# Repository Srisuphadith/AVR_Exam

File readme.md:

# Oscilloscope and Component tester
### CPE324 Embedded System
### Member
- 66070501027 NOPPANUT PRASERTWONGSA
- 66070501052 SRISUPHADITH RATTANAPRASERT
- 66070501053 SAKCHAT HENSOOK
- 66070501060 ADISORN PARAMA

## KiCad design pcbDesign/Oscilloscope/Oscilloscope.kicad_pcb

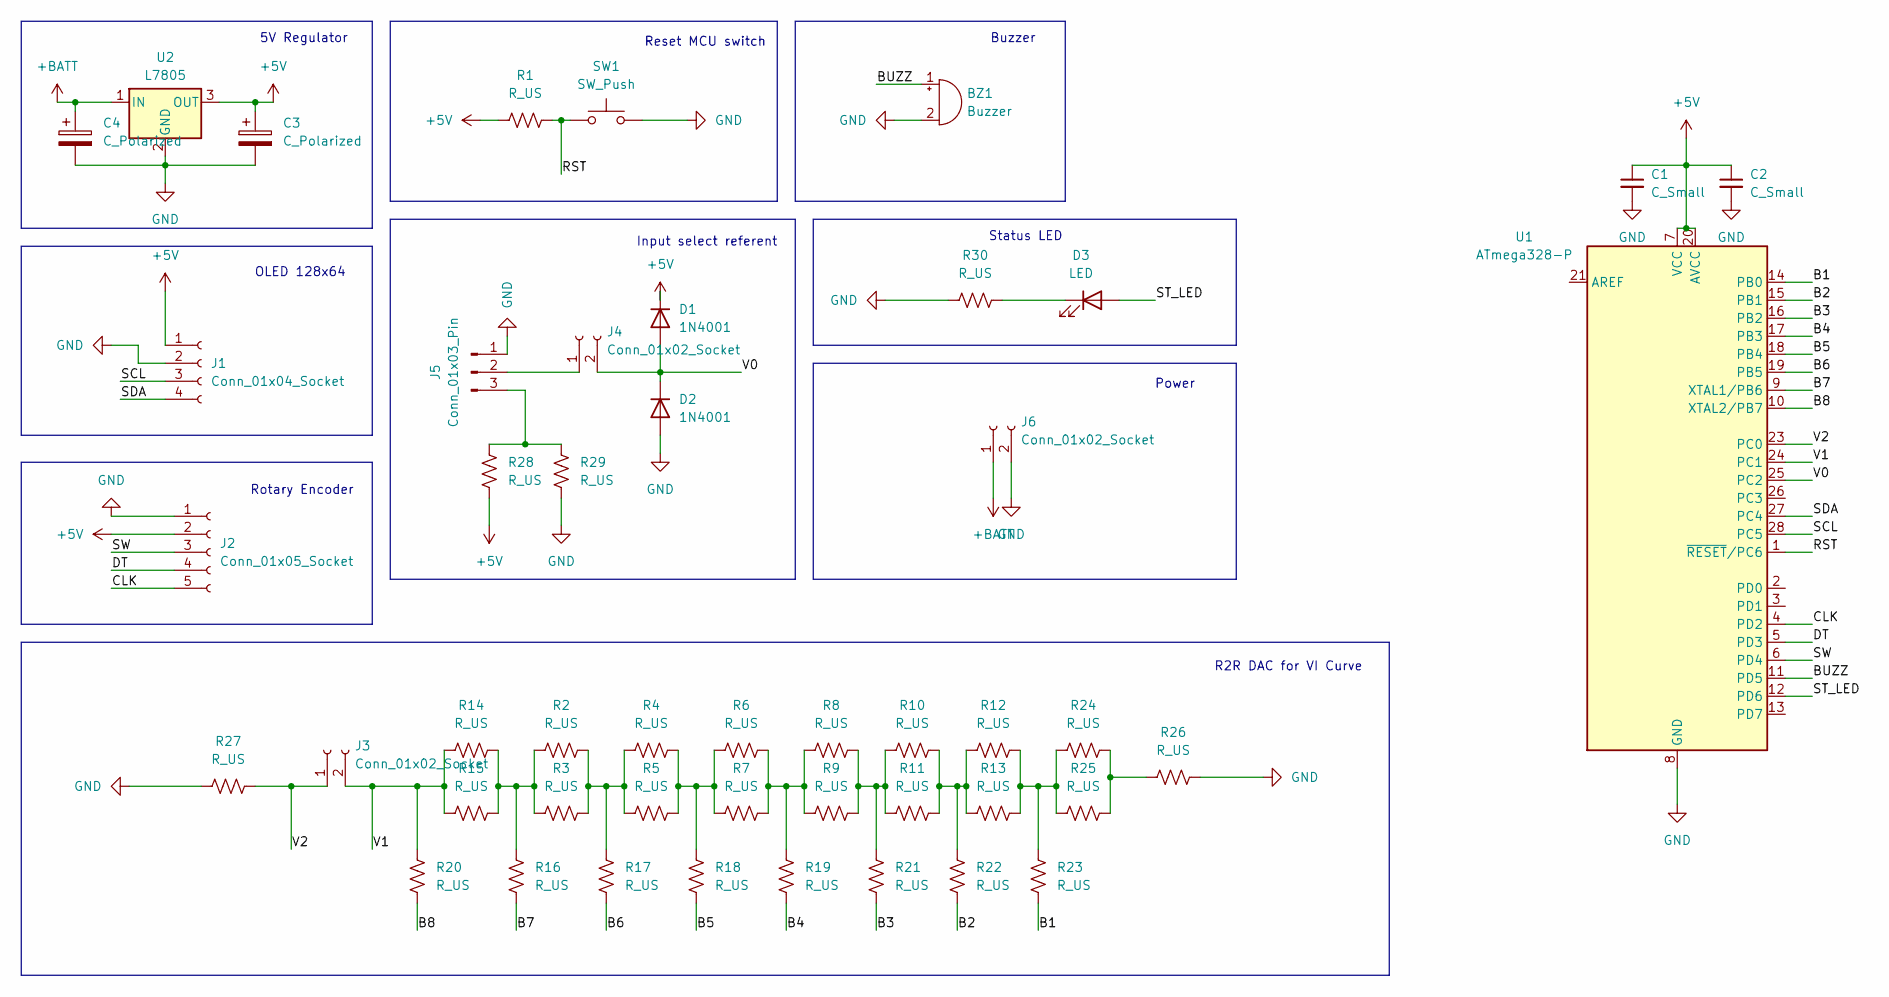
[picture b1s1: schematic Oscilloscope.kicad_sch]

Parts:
BZ1: Buzzer; Buzzer_12x9.5RM7.6
C1, C2: C_Small; C_Disc_D6.0mm_W2.5mm_P5.00mm
C3, C4: C_Polarized; CP_Radial_D6.3mm_P2.50mm
D1, D2: 1N4001; D_DO-34_SOD68_P7.62mm_Horizontal
D3: LED; LED_D3.0mm_FlatTop
J1: Conn_01x04_Socket; PinHeader_1x04_P2.54mm_Vertical
J2: Conn_01x05_Socket; PinHeader_1x05_P2.54mm_Vertical
J3, J4, J6: Conn_01x02_Socket; PinHeader_1x02_P2.54mm_Vertical
J5: Conn_01x03_Pin; PinHeader_1x03_P2.54mm_Vertical
R1, R2, R3, R4, R5, R6, R7, R8, R9, R10, R11, R12, R13, R14, R15, R16, R17, R18, R19, R20, R21, R22, R23, R24, R25, R26, R27, R28, R29, R30: R_US; R_Axial_DIN0207_L6.3mm_D2.5mm_P7.62mm_Horizontal
SW1: SW_Push; SW_PUSH_6mm_H4.3mm
U1: ATmega328-P; DIP-28_W7.62mm
U2: L7805; PinHeader_1x03_P2.54mm_Vertical

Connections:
+5V: C1.1, C2.1, C3.1, D1.1 (K), J1.1, J2.2, R1.1, R28.2, U1.7 (VCC), U1.20 (AVCC), U2.3 (OUT)
+BATT: C4.1, J6.1, U2.1 (IN)
/B1: R23.2, U1.14 (PB0)
/B2: R22.2, U1.15 (PB1)
/B3: R21.2, U1.16 (PB2)
/B4: R19.2, U1.17 (PB3)
/B5: R18.2, U1.18 (PB4)
/B6: R17.2, U1.19 (PB5)
/B7: R16.2, U1.9 (XTAL1/PB6)
/B8: R20.2, U1.10 (XTAL2/PB7)
/BUZZ: BZ1.1 (+), U1.11 (PD5)
/CLK: J2.5, U1.4 (PD2)
/DT: J2.4, U1.5 (PD3)
/RST: R1.2, SW1.1, U1.1 (~RESET/PC6)
/SCL: J1.3, U1.28 (PC5)
/SDA: J1.4, U1.27 (PC4)
/ST_LED: D3.2 (A), U1.12 (PD6)
/SW: J2.3, U1.6 (PD4)
/V0: D1.2 (A), D2.1 (K), J4.2, U1.25 (PC2)
/V1: J3.2, R14.1, R15.1, R20.1, U1.24 (PC1)
/V2: J3.1, R27.2, U1.23 (PC0)
GND: BZ1.2 (-), C1.2, C2.2, C3.2, C4.2, D2.2 (A), J1.2, J2.1, J5.1, J6.2, R26.2, R27.1, R29.2, R30.2, SW1.2, U1.8 (GND), U1.22 (GND), U2.2 (GND)
unnamed: D3.1 (K), R30.1
unnamed: J4.1, J5.2
unnamed: J5.3, R28.1, R29.1
unnamed: R8.2, R9.2, R10.1, R11.1, R21.1
unnamed: R10.2, R11.2, R12.1, R13.1, R22.1
unnamed: R12.2, R13.2, R23.1, R24.1, R25.1
unnamed: R2.1, R3.1, R14.2, R15.2, R16.1
unnamed: R2.2, R3.2, R4.1, R5.1, R17.1
unnamed: R4.2, R5.2, R6.1, R7.1, R18.1
unnamed: R6.2, R7.2, R8.1, R9.1, R19.1
unnamed: R24.2, R25.2, R26.1

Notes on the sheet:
Power
OLED 128x64
Rotary Encoder
Input select referent
Status LED
R2R DAC for VI Curve
Buzzer
Reset MCU switch
5V Regulator

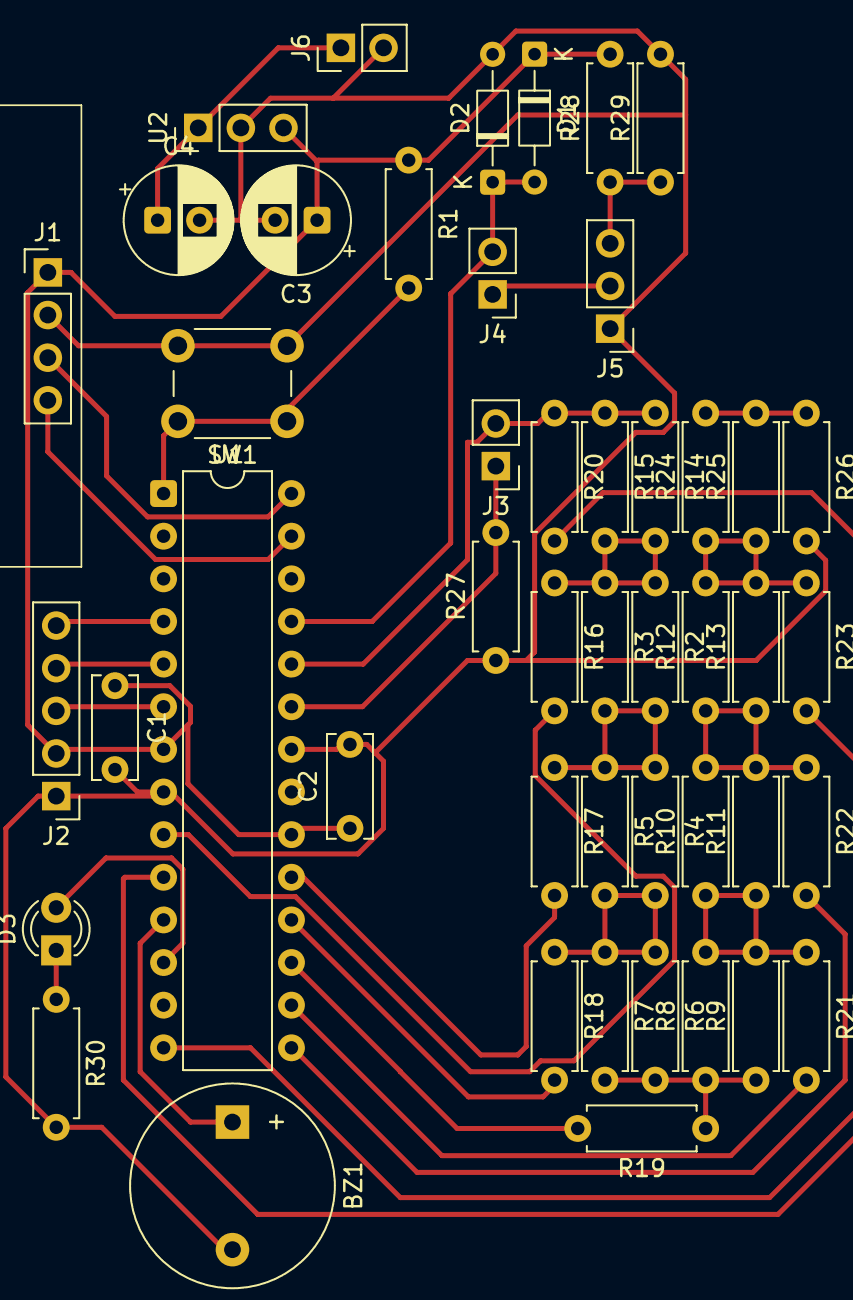
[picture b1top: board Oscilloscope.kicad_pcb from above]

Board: 2 copper layers, 47 parts (0 on the bottom side), 33 nets.

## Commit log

2026-04-18 initial
2026-04-18 add all module
2026-04-18 change little bit
2026-04-18 add readme
2026-04-18 edit md
2026-04-18 edit doc
2026-04-19 example exam
2026-04-20 optm dir
2026-04-27 exam
2026-05-04 oscilloscope
2026-05-04 version2
2026-05-04 refactor DAC
2026-05-04 schema
2026-05-07 change port
2026-05-08 test_DAC
2026-05-08 comment
2026-05-08 try vi curve
2026-05-09 fix interrupt failure
2026-05-09 test vi curve
2026-05-09 optimize space
2026-05-09 refactor
2026-05-11 refactor2
2026-05-11 Wai oled char function
2026-05-11 vi with draw line
2026-05-11 reset when change mode
2026-05-12 add draw line to oscilloscope mode to represent rectangle wave
2026-05-12 redirectory
